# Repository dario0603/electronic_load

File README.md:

# Electronic Load

<p align="left">

</p>

Un progetto open-source per la progettazione e simulazione di un **Carico Elettronico Bipolare** (Electronic Load), ideato per il test e la caratterizzazione di alimentatori, batterie e circuiti di potenza.

---

## Caratteristiche del Progetto

* **Simulazioni LTspice**: Analisi del comportamento dinamico e della risposta del circuito di controllo.
* **Sbrogliato KiCad**: Schemi elettrici e layout PCB completi per la realizzazione dell'hardware.
* **Modalità di funzionamento**: Progettato per operare in corrente costante (*CC*).

---

## Struttura del Repository

```text
electronic_load/
├── LTspice/       # File di simulazione (.asc, .plt)
├── KiCad/         # Schemi (.kicad_sch) e PCB (.kicad_pcb)
└── README.md

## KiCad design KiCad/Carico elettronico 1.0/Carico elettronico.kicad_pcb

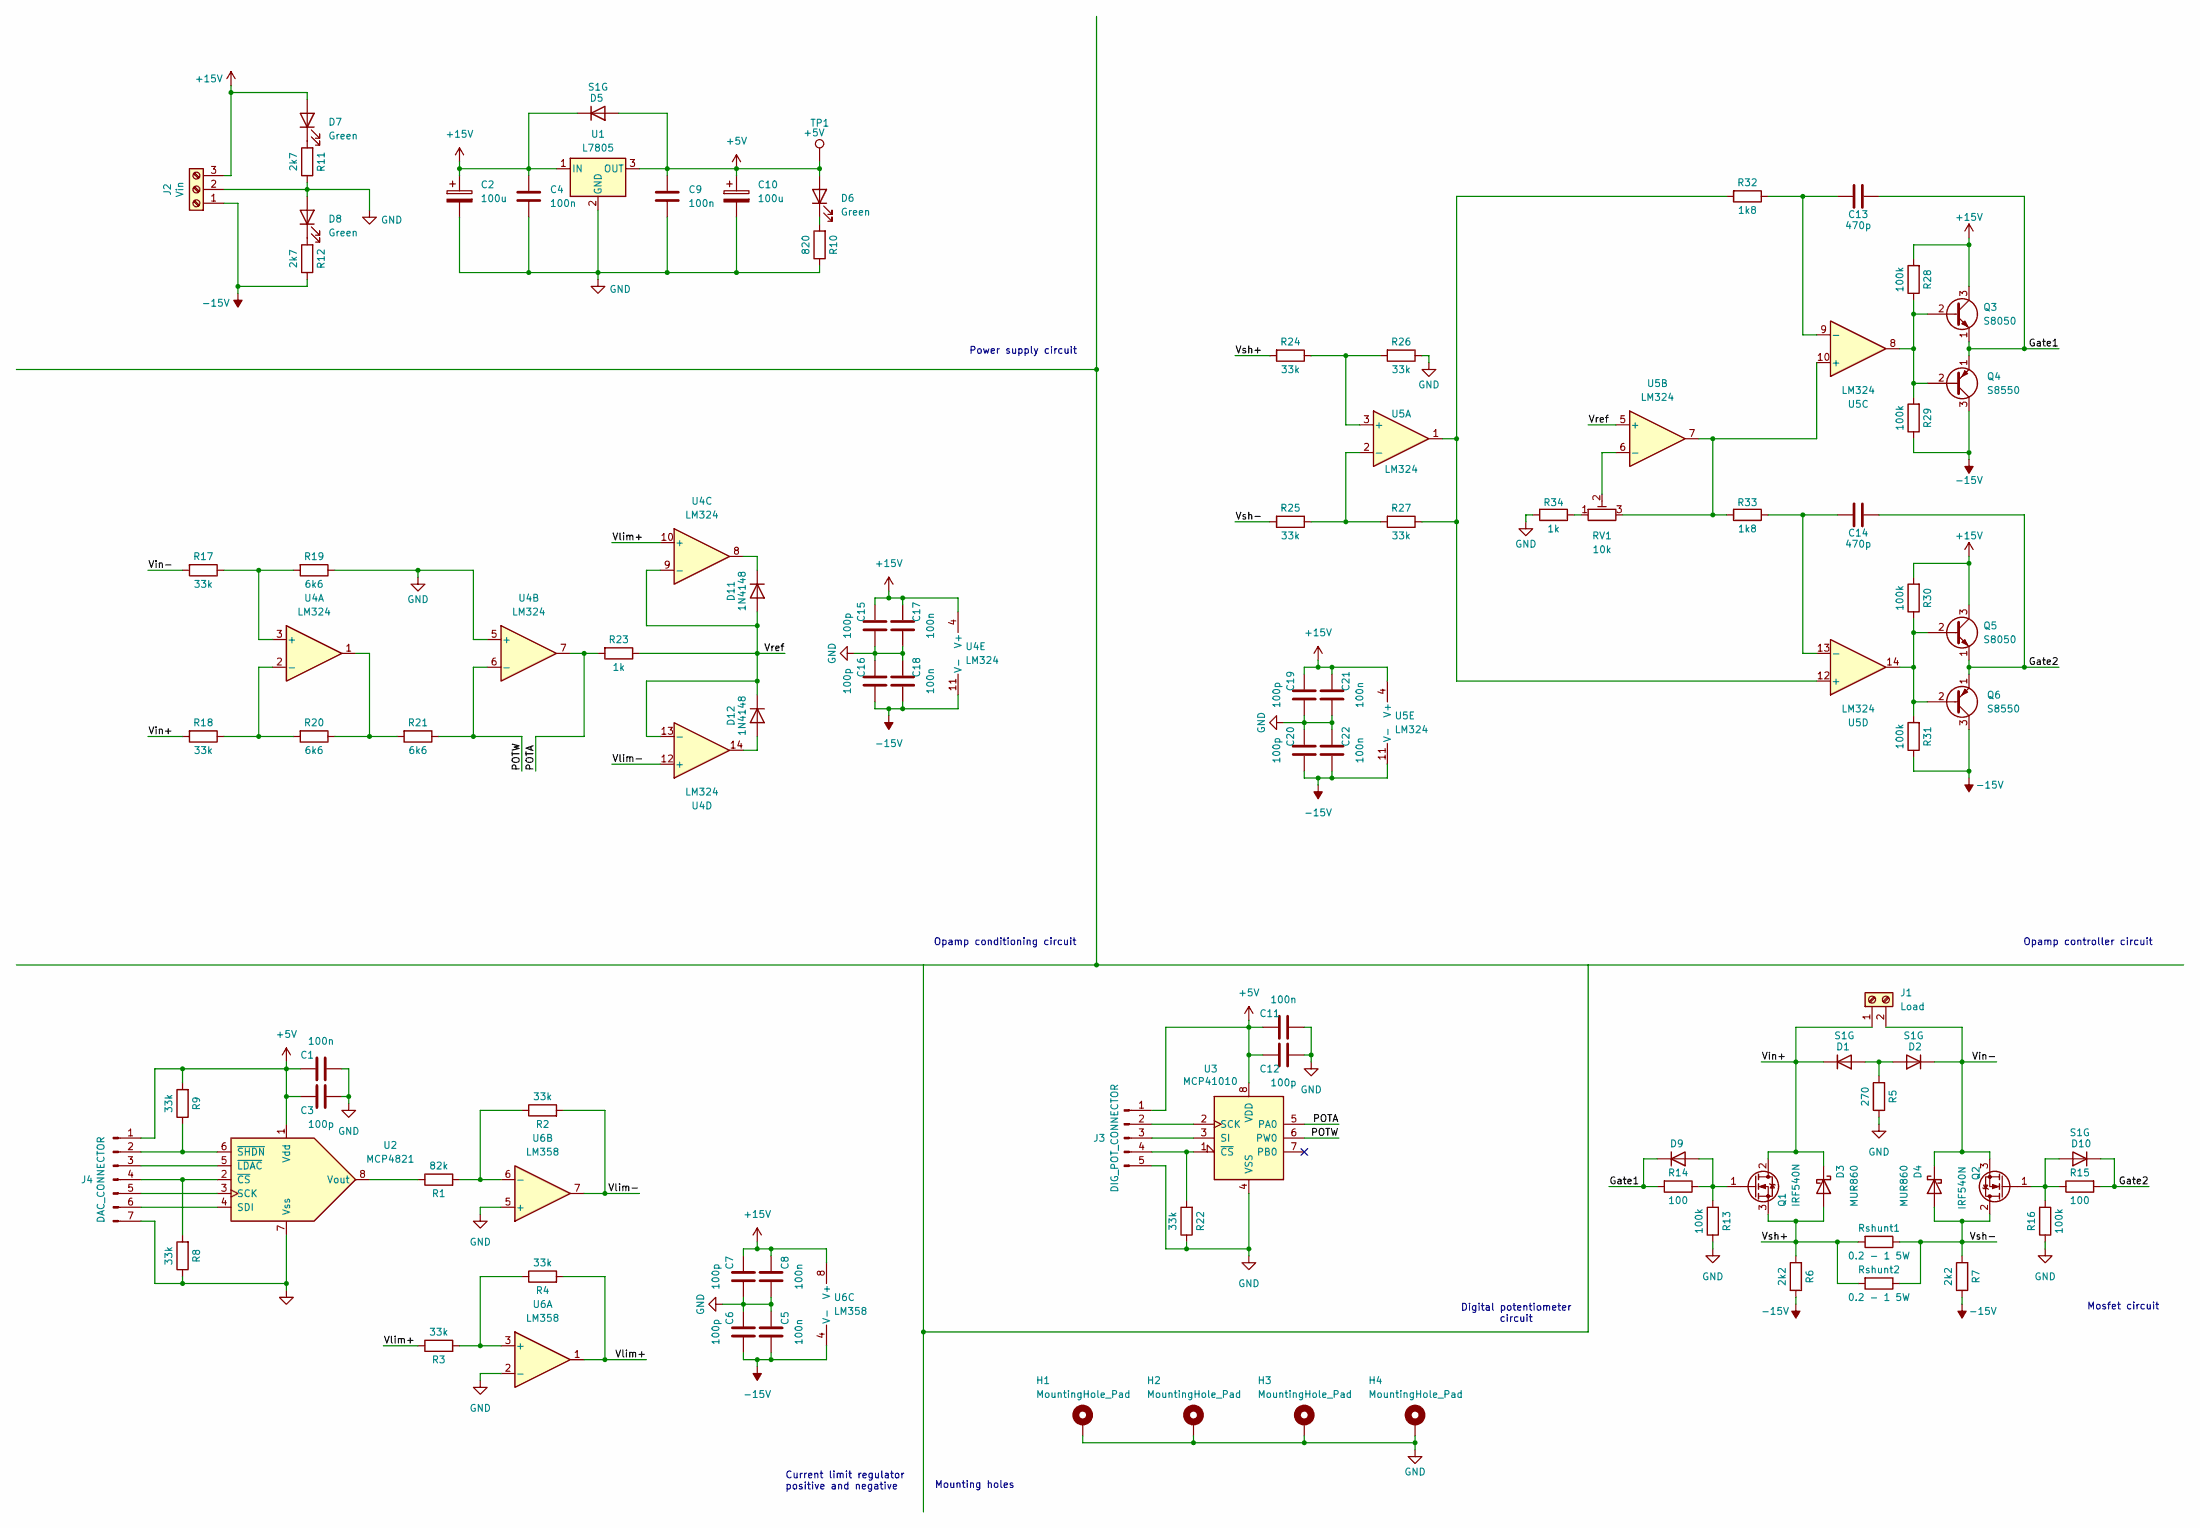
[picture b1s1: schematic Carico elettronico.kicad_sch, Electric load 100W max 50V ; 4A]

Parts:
C1, C4, C5, C8, C9, C11, C17, C18, C21, C22: 100n; C_0805_2012Metric_Pad1.18x1.45mm_HandSolder
C2, C10: 100u; CP_Elec_8x10.5
C3, C6, C7, C12, C15, C16, C19, C20: 100p; C_0805_2012Metric_Pad1.18x1.45mm_HandSolder
C13, C14: 470p; C_0805_2012Metric_Pad1.18x1.45mm_HandSolder
D1, D2, D5, D9, D10: S1G; D_SMA_Handsoldering
D3, D4: MUR860; TO-220-2_Vertical
D6, D7, D8: Green; LED_0805_2012Metric_Pad1.15x1.40mm_HandSolder
D11, D12: 1N4148; D_SOD-323F
H1, H2, H3, H4: MountingHole_Pad; MountingHole_3.2mm_M3_DIN965_Pad
J1: Load; TerminalBlock_Phoenix_MKDS-1,5-2-5.08_1x02_P5.08mm_Horizont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
J2: Vin; TerminalBlock_Phoenix_MKDS-1,5-3-5.08_1x03_P5.08mm_Horizont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
J3: DIG_POT_CONNECTOR; PinHeader_1x05_P2.54mm_Vertical
J4: DAC_CONNECTOR; PinHeader_1x07_P2.54mm_Vertical
Q1, Q2: IRF540N; TO-220-3_Vertical
Q3, Q5: S8050; SOT-23
Q4, Q6: S8550; SOT-23
R1: 82k; R_0805_2012Metric_Pad1.20x1.40mm_HandSolder
R2, R3, R4, R8, R9, R17, R18, R22, R24, R25, R26, R27: 33k; R_0805_2012Metric_Pad1.20x1.40mm_HandSolder
R5: 270; R_0805_2012Metric_Pad1.20x1.40mm_HandSolder
R6, R7: 2k2; R_0805_2012Metric_Pad1.20x1.40mm_HandSolder
R10: 820; R_0805_2012Metric_Pad1.20x1.40mm_HandSolder
R11, R12: 2k7; R_0805_2012Metric_Pad1.20x1.40mm_HandSolder
R13, R16, R28, R29, R30, R31: 100k; R_0805_2012Metric_Pad1.20x1.40mm_HandSolder
R14, R15: 100; R_0805_2012Metric_Pad1.20x1.40mm_HandSolder
R19, R20, R21: 6k6; R_0805_2012Metric_Pad1.20x1.40mm_HandSolder
R23, R34: 1k; R_0805_2012Metric_Pad1.20x1.40mm_HandSolder
R32, R33: 1k8; R_0805_2012Metric_Pad1.20x1.40mm_HandSolder
RV1: 10k; Potentiometer_Bourns_3296W_Vertical
Rshunt1, Rshunt2: 0.2 - 1 5W; R_Radial_Power_L16.1mm_W9.0mm_P7.37mm
TP1: +5V; TestPoint_Pad_D1.0mm
U1: L7805; TO-252-2
U2: MCP4821; SOIC-8_3.9x4.9mm_P1.27mm
U3: MCP41010; SOIC-8_3.9x4.9mm_P1.27mm
U4, U5: LM324; SOIC-14_3.9x8.7mm_P1.27mm
U6: LM358; SOIC-8_3.9x4.9mm_P1.27mm

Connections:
+5V: C1.1, C3.1, C9.1, C10.1, C11.1, C12.1, D5.2 (A), D6.2 (A), J3.1, J4.1, R9.2, TP1.1, U1.3 (OUT), U2.1 (Vdd), U3.8 (VDD)
+15V: C2.1, C4.1, C7.1, C8.1, C15.1, C17.1, C19.1, C21.1, D5.1 (K), D7.2 (A), J2.3, Q3.3 (C), Q5.3 (C), R28.2, R30.2, U1.1 (IN), U4.4 (V+), U5.4 (V+), U6.8 (V+)
-15V: C5.2, C6.2, C16.2, C18.2, C20.2, C22.2, J2.1, Q4.3 (C), Q6.3 (C), R6.1, R7.1, R12.1, R29.1, R31.1, U4.11 (V-), U5.11 (V-), U6.4 (V-)
/Gate1: C13.2, D9.1 (K), Q3.1 (E), Q4.1 (E), R14.2
/Gate2: C14.2, D10.1 (K), Q5.1 (E), Q6.1 (E), R15.2
/POTA: R23.2, U3.5 (PA0), U4.7
/POTW: R21.1, U3.6 (PW0), U4.6 (-)
/Vin+: D1.1 (K), D3.1 (K), J1.1, Q1.2 (D), R18.2
/Vin-: D2.1 (K), D4.1 (K), J1.2, Q2.3 (S), R17.2
/Vlim+: R3.1, R4.2, U4.10 (+), U6.1
/Vlim-: R2.2, U4.12 (+), U6.7
/Vref: D11.2 (A), D12.1 (K), R23.1, U4.9 (-), U4.13 (-), U5.5 (+)
/Vsh+: D3.2 (A), Q1.3 (S), R6.2, R24.2, Rshunt1.2, Rshunt2.2
/Vsh-: D4.2 (A), Q2.2 (D), R7.2, R25.2, Rshunt1.1, Rshunt2.1
GND: C1.2, C2.2, C3.2, C4.2, C5.1, C6.1, C7.2, C8.2, C9.2, C10.2, C11.2, C12.2, C15.2, C16.1, C17.2, C18.1, C19.2, C20.1, C21.2, C22.1, D8.2 (A), H1.1, H2.1, H3.1, H4.1, J2.2, J3.5, J4.7, R5.1, R8.1, R10.1, R11.1, R13.1, R16.1, R19.1, R22.1, R26.1, R34.2, U1.2 (GND), U2.7 (Vss), U3.4 (VSS), U4.5 (+), U6.2 (-), U6.5 (+)
unnamed: D1.2 (A), D2.2 (A), R5.2
unnamed: D6.1 (K), R10.2
unnamed: D7.1 (K), R11.2
unnamed: D8.1 (K), R12.2
unnamed: D9.2 (A), Q1.1 (G), R13.2, R14.1
unnamed: D10.2 (A), Q2.1 (G), R15.1, R16.2
unnamed: D11.1 (K), U4.8
unnamed: D12.2 (A), U4.14
unnamed: J3.2, U3.2 (SCK)
unnamed: J3.3, U3.3 (SI)
unnamed: J3.4, R22.2, U3.1 (~CS)
unnamed: J4.2, R9.1, U2.6 (~SHDN)
unnamed: J4.3, U2.5 (~LDAC)
unnamed: J4.4, R8.2, U2.2 (~CS)
unnamed: J4.5, U2.3 (SCK)
unnamed: J4.6, U2.4 (SDI)
unnamed: Q3.2 (B), Q4.2 (B), R28.1, R29.2, U5.8
unnamed: Q5.2 (B), Q6.2 (B), R30.1, R31.2, U5.14
unnamed: R20.1, R21.2, U4.1
unnamed: R34.1, RV1.1
unnamed: R1.1, U2.8 (Vout)
unnamed: R17.1, R19.2, U4.3 (+)
unnamed: R18.1, R20.2, U4.2 (-)
unnamed: R24.1, R26.2, U5.3 (+)
unnamed: R25.1, R27.2, U5.2 (-)
unnamed: RV1.2, U5.6 (-)
unnamed: R33.2, RV1.3, U5.7, U5.10 (+)
unnamed: C13.1, R32.1, U5.9 (-)
unnamed: R27.1, R32.2, U5.1, U5.12 (+)
unnamed: C14.1, R33.1, U5.13 (-)
unnamed: R3.2, R4.1, U6.3 (+)
unnamed: R1.2, R2.1, U6.6 (-)

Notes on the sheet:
Digital potentiometer circuit
Opamp controller circuit
Power supply circuit
Mosfet circuit
Opamp conditioning circuit
Current limit regulator positive and negative
Mounting holes

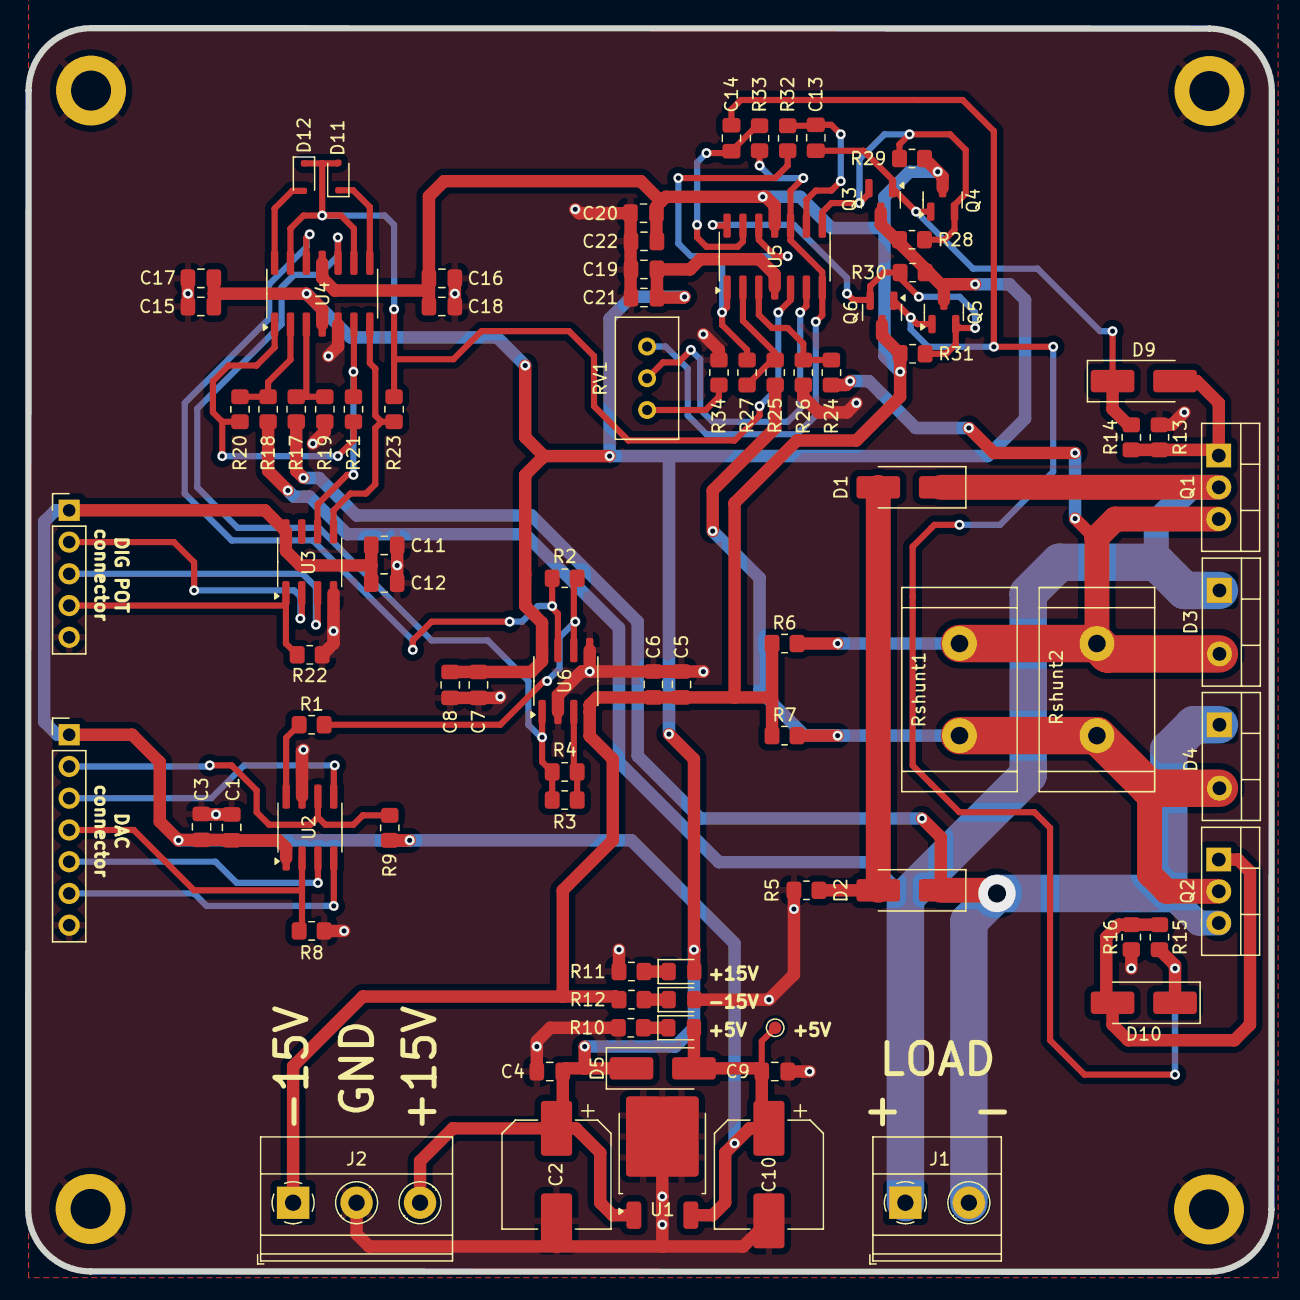
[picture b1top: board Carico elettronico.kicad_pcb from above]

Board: 2 copper layers, 99.5 x 99.5 mm, 92 parts (0 on the bottom side), 47 nets.
